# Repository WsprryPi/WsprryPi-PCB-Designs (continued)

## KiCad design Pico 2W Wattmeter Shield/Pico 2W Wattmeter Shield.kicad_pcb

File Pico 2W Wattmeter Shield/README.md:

# Pico 2W QRP Wattmeter Shield

A Raspberry Pi Pico 2 W shield with an ADL5904 RF power detector, ADS1115 ADC, and TPS7A2033 analog regulator. Open [Pico 2W Wattmeter Shield.kicad_pro](Pico%202W%20Wattmeter%20Shield.kicad_pro) in KiCad 10. Project libraries use `${KIPRJMOD}` paths.

The design is supplied **as is, without warranty**, under the repository's [MIT license](../LICENSE.md). It is an experimental system. Production use requires an operator who understands its limitations and requirements and verifies the assembled system's suitability. See the [repository notice](../README.md#experimental-use-and-warranty).

## Current design

The PCB is a two-layer, nominally 1.6 mm FR4 board with circuit components on F.Cu and U10's two female socket strips on B.Cu, matching the [Pico shield template](../Pico%202W%20Shield%20Template/README.md). It contains **37 footprints: 34 automatic SMT components, J30, U10, and one front silkscreen logo**. The components, including the R63/C61 pull-up supply filter, are placed and routed.

Assembled input match, accuracy, noise rejection, mechanical fit, and the soldering process are unqualified. ERC ignores single-use global labels, four-way junctions, simulation model issues, and footprint-filter mismatches; DRC has no ignored checks.

## Measurement path

`J30 → C30–C34 → RF_DET_IN → C40–C44 → RFIN/U40 → VRMS_RAW → R50/C50 → VRMS_FILTERED/U60 AIN0`

| Section | Saved design |
| --- | --- |
| RF input | J30; terminating low-power meter, with external attenuation for amplifier outputs |
| Coupling | Two banks of five parallel 100 nF C0G capacitors, nominally 500 nF per bank |
| Shunt load | R30–R34: five parallel 412 Ω resistors, nominally 82.4 Ω, plus the detector input branch |
| Input matching | The shunt is within 0.12% of ADI's 82.5 Ω reference; assembled input impedance is unmeasured |
| Intended frequency range | 136 kHz–450 MHz, covering 2200 m through 70 cm; assembled-board coverage is unqualified |
| Nominal detector range | −30 to +15 dBm, approximately 1 µW–31.6 mW; connector range requires calibration |
| ADC filter | R50 = 470 Ω, C50 = 22 µF X5R; nominal cutoff 15.4 Hz |

There is no onboard attenuation pad or qualified high-power overload protection. The two capacitor banks, buses, launch, and detector impedance form a frequency-dependent RF network. See [input range and measurement conditions](INPUT-RANGE.md). The printed current range is calculated for a nominal 50 Ω load, rather than a direct current measurement.

## Power

**The analog section requires VBUS.** U20 takes VBUS from Pico pin 40 and generates `ANALOG_3V3` for U40, U60, and the I²C pullups. C20 and C21 are 2.2 µF, 25 V X7R capacitors at the regulator input and output. C46/C47 decouple the detector, and C60 decouples the ADC. The Pico's 3V3 output is not connected to the analog rail.

USB normally supplies VBUS. Powering the Pico solely through VSYS leaves the analog section unpowered. An external VBUS source must respect the Pico's USB power arrangement and avoid conflicting supplies. Measurements require a valid analog rail and settled detector/filter output.

VBUS follows the lower perimeter, and the analog rail reaches the detector from below and the ADC/control branch from the right. Neither supply trace crosses the RF capacitor-bank area. R63/C61 isolate the pull-up supply branch. A common regulator and ground serve the analog and I²C loads; noise immunity to Pico activity is unmeasured.

## ADC and filtering

U60 uses AIN0 as a single-ended detector-voltage input. ADDR is grounded, giving I²C address 0x48. SDA uses GP4; SCL uses GP5 through the fitted R62 0 Ω jumper. R60/R61 are 4.7 kΩ pullups supplied through R63 = 47 Ω, with C61 = 1 µF X7R providing local bypass at their common supply node. This filter is present in both schematic and PCB. U40 and U60 receive `ANALOG_3V3` directly with their own decoupling. Unused ADC channels and ALERT/RDY have no-connect flags.

R63/C61 has a nominal **3.4 kHz** corner and approximately **65 mV** supply drop with both pull-ups low, assuming ideal low output levels. It provides local storage and supply isolation for switching currents. Its effect on the assembled noise floor is unmeasured; nominal attenuation at 50/60 Hz is negligible.

R50/C50 passes DC and attenuates changing voltage. Its ideal one-pole attenuation is about **10.6 dB at 50 Hz and 12.1 dB at 60 Hz**, with a 10.34 ms time constant and about 47.6 ms settling to 1%. Capacitor tolerance, bias, temperature, detector output impedance, and ADC loading affect these figures. It is not a mains notch filter, and there is no established system-level mains-rejection specification. C49 remains a separate 10 nF capacitor directly on VRMS.

The hardware provides one measurement channel. ADC range, conversion rate, timed averaging, and calibration coefficients are application settings; this repository does not establish a verified wattmeter firmware configuration.

## Current assembly and fabrication

Factory assembly comprises **34 components on F.Cu**: **C20–C21, C30–C34, C40–C50, C60–C61; R30–R34, R40, R50, R60–R63; U20, U40, U60**. This is 20 capacitors, 11 resistors, and three ICs. J30, two female sockets, and the Pico module are fitted by hand. U10 represents the combined 40-pad socket interface; schematic J10/J11 are pinless purchasing descriptions. The front logo and manual parts are excluded from automatic SMT assembly.

The **Shield purchasing BOM** preset uses `LCSC Part #`. All 34 schematic and PCB SMT parts have matching manufacturer, MPN, and LCSC identifiers. R30–R34 specify Viking ARG02BTC4120 / C2683017 in local 0402 footprints. R63 specifies YAGEO RC0402FR-0747RL / C137973 in 0402; C61 specifies YAGEO CC0603KRX7R8BB105 / C106858 in 0603. Factory BOM and placement exports must contain the same 34 references and correct U20/U40/U60 pin-1 orientation. The schematic contains the complete part selections. The input-range silkscreen displays J30 through a reference variable and follows reannotation.

Seven selected through vias use **0.60 mm copper / 0.25 mm drill** with filling/capping enabled, F-side untented, and B-side tented: five in U40's exposed ground pad and one each centered on R40 pad 1 and C48 pad 1. The unique drill size identifies this selective process. The 17 ordinary vias comprise five 0.50/0.20 mm, ten 0.60/0.30 mm, and two 0.80/0.40 mm vias. All 24 are through vias; the custom rules disallow blind, buried, and microvias. The ordinary ground-via drills beside C45/C47 have **0.15 mm nominal clearance** from the adjacent component solder-pad openings.

The required fabrication process is selective nonconductive epoxy filling, planarization, and copper capping. Its availability for this exact two-layer order is not confirmed. Four separate 0.65 × 0.65 mm F.Paste windows cover 52.16% of U40's 1.8 × 1.8 mm ground land. Supplier process acceptance, stencil thickness, and reflow conditions are assembly requirements.

- [Fabrication and assembly requirements](manufacturing-notes/ORDER-NOTES.txt)
- [Front assembly map](manufacturing-notes/ASSEMBLY-FRONT.svg)
- [Selective via-treatment drawing](manufacturing-notes/U1-VIA-TREATMENT.svg)
- [U40 exposed-pad and stencil geometry](U1-PASTE-WINDOWS.md)
- [SMA connector and board-edge fit](J1-CONNECTOR-NOTES.md)
- [Pico sockets and antenna notch](PICO-HEADERS-AND-NOTCH.md)

The manufacturing drawings identify their source PCB by SHA-256. Socket lead fit and mating height are unspecified. The PCB stackup's copper-finish field is `None`, and there are no dedicated board fiducials; finish and panel tooling belong in the order specification.

## Pico interface placement

U10 is locked at **(146.810, 90.750) mm, −90°, B.Cu**, and its `Raspberry Pi Pico 2W` group is locked. Its 40 pad positions match the template. The notch spans x = 164.46–173.46 mm and y = 82.86–96.86 mm, with a copper/component keepout on both layers.

In **Update PCB from Schematic**, leave **Re-link footprints to schematic symbols based on their reference designators** and **Override locks** unchecked. Normal symbol-ID matching preserves the interface identity and placement. [KiCad's update documentation](https://docs.kicad.org/10.0/en/pcbnew/pcbnew.html#updating_the_board_from_the_schematic) describes these options.

The two socket models belong to U10's combined footprint and use project-local paths. The reusable footprint contains the same references. The socket geometry is a generic preview, without a selected manufacturer or qualified mating stack.

## Libraries and 3D view

Local assets are in `pico-wattmeter.pretty/`, `pico-wattmeter.kicad_sym`, `pico-wattmeter.kicad_blocks/`, and `pico-wattmeter.3dshapes/`. See [footprint sources and licenses](pico-wattmeter.pretty/LIBRARY-SOURCES.md) and [model sources and limits](pico-wattmeter.3dshapes/README.md).

Select **View > 3D Viewer** in the PCB Editor. U40 uses the local CP-16-22 STEP model. U10 uses two local socket models. J30 uses the local illustrative Adafruit 1865 SMA model, pointing outward from the left board edge. Passives, U20, and U60 use installed KiCad models. All placed model references resolve in the checked KiCad installation.

The optional, unplaced Pico SMD footprint uses `${KIPRJMOD}/pico-2w-libs/Raspberrypi pico2 W.step`. That separate reference collection has [pin/pad, model-alignment, and provenance limitations](pico-2w-libs/README.md). It is not the placed socket interface.

`fabrication-toolkit-options.json` stores export preferences. KiCad sources contain the part identifiers, connectivity, layout, and assembly exclusions. Local preferences, backups, plugin state, and generated export directories are ignored by Git.

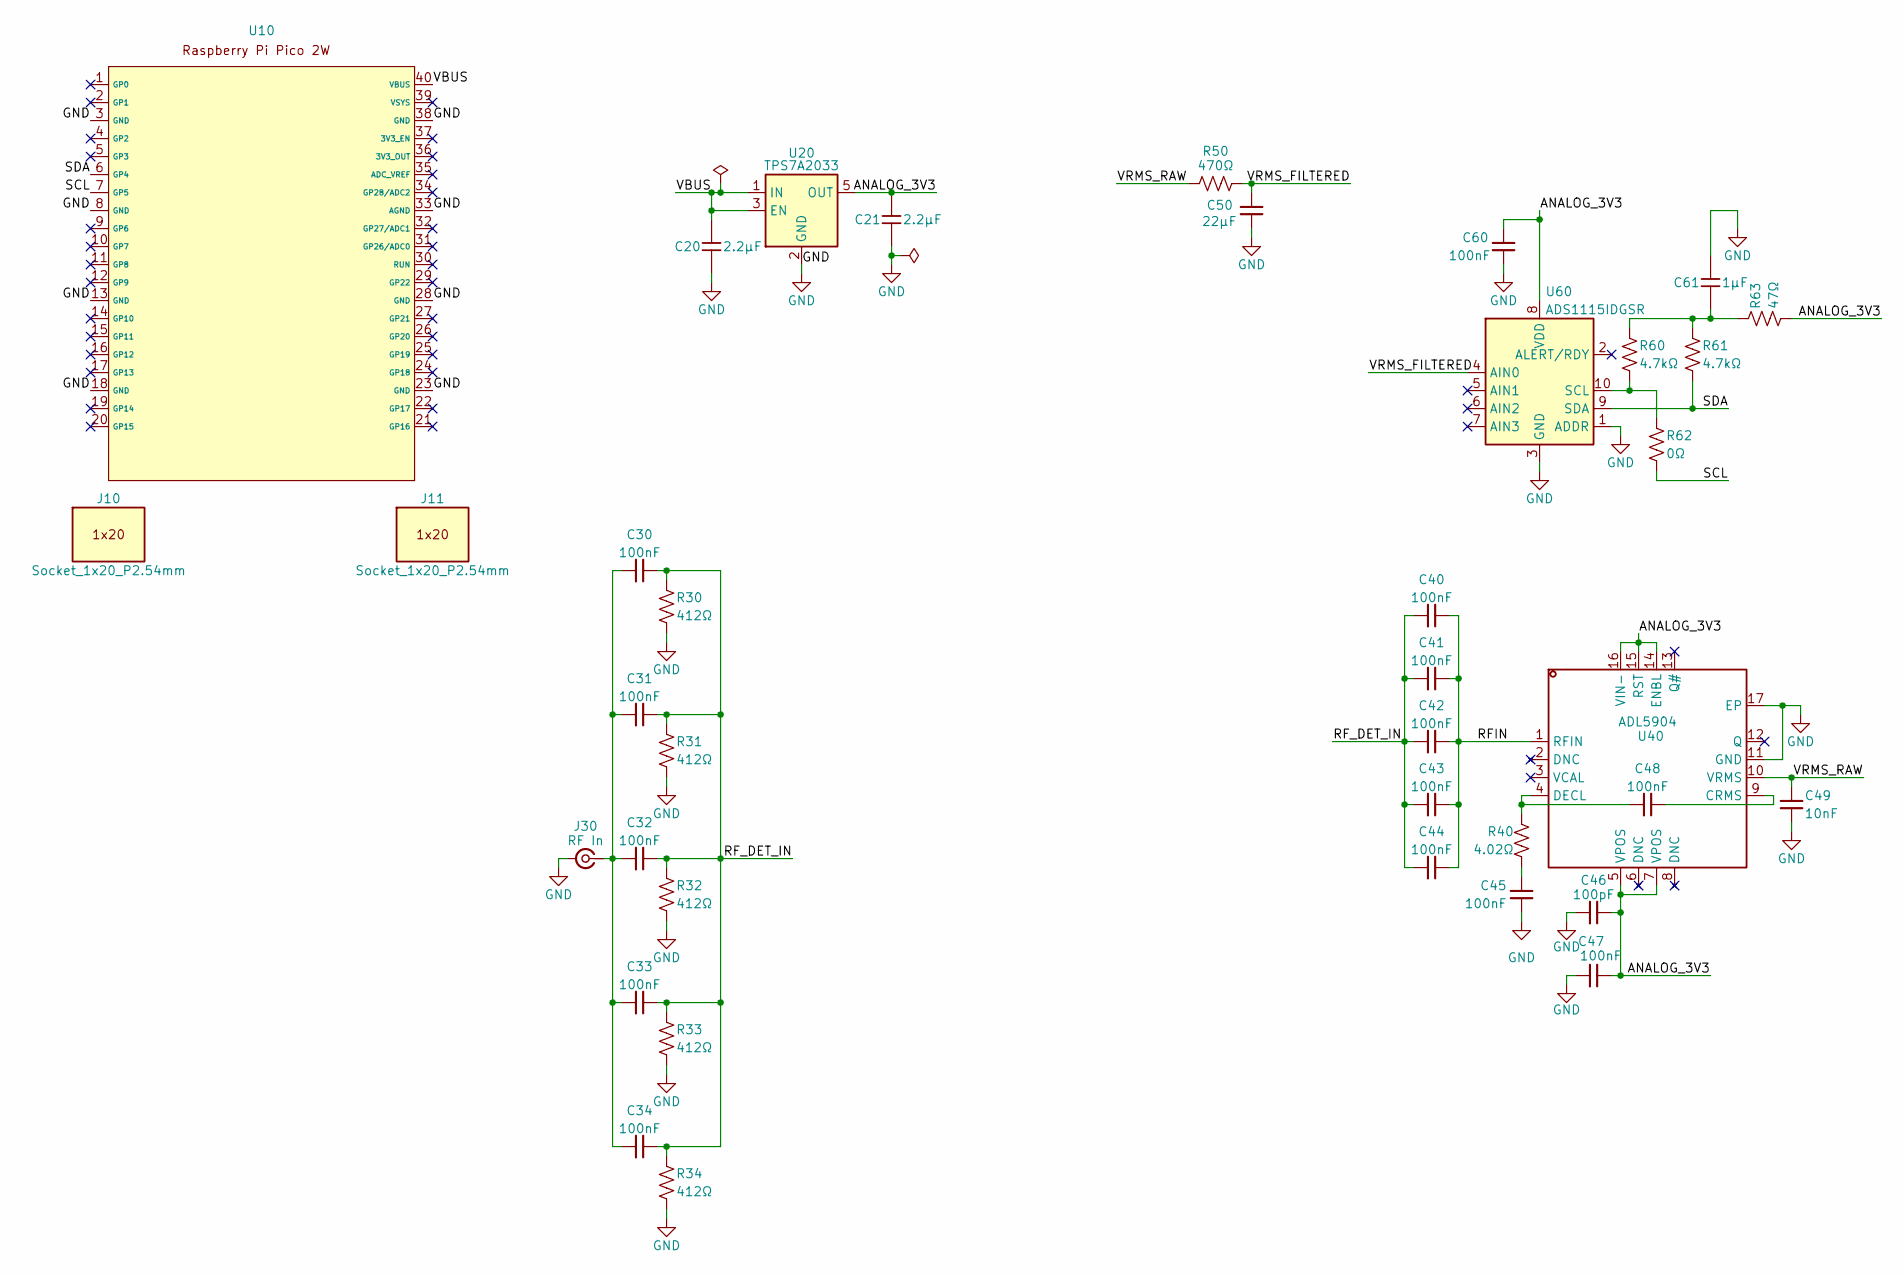
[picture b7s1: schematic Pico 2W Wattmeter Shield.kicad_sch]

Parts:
C20, C21: 2.2μF; C_0805_2012Metric; Tolerance 10%; Rating 25 V; MPN CC0805KKX7R8BB225; LCSC Part # C277470
C30, C31, C32, C33, C34, C40, C41, C42, C43, C44, C48: 100nF; C_1206_3216Metric; MPN 1206N104J500CT; LCSC Part # C170182
C45, C47, C60: 100nF; C_0402_1005Metric; MPN CL05B104KO5NNNC; LCSC Part # C1525
C46: 100pF; C_0402_1005Metric; MPN 0402CG101J500NT; LCSC Part # C1546
C49: 10nF; C_0402_1005Metric; MPN CL05B103KB5NNNC; LCSC Part # C15195
C50: 22µF; C_0805_2012Metric; MPN CL21A226MAYNNNE; LCSC Part # C602037
C61: 1μF; C_0603_1608Metric; Tolerance 10%; Rating 25 V; MPN CC0603KRX7R8BB105; LCSC Part # C106858
J10, J11: Socket_1x20_P2.54mm
J30: RF In; SMA_Adafruit_1865_EdgeMount; MPN 1865
R30, R31, R32, R33, R34: 412Ω; R_0402_1005Metric; MPN ARG02BTC4120; LCSC Part # C2683017
R40: 4.02Ω; R_0402_1005Metric; MPN FRC0402F4R02TS; LCSC Part # C55174786
R50: 470Ω; R_0402_1005Metric; MPN FRC0402F4700TS; LCSC Part # C2909361
R60, R61: 4.7kΩ; R_0402_1005Metric; MPN 0402WGF4701TCE; LCSC Part # C25900
R62: 0Ω; R_0805_2012Metric; MPN 0805W8F0000T5E; LCSC Part # C17477
R63: 47Ω; R_0402_1005Metric; MPN RC0402FR-0747RL; LCSC Part # C137973
U10: Raspberry_Pi_Pico_2W_Header
U20: TPS7A2033; SOT-23-5; Tolerance Datasheet; Rating 300 mA device rating; MPN TPS7A2033PDBVR; LCSC Part # C2862740
U40: ADL5904; QFN-16_L3.0-W3.0-P0.50-TL-EP1.8; MPN ADL5904ACPZN-R7; LCSC Part # C206813
U60: ADS1115IDGSR; TSSOP-10_3x3mm_P0.5mm; MPN ADS1115IDGSR; LCSC Part # C37593

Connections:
/ANALOG_3V3: C21.1, C46.2, C47.1, C60.2, R63.2, U20.5 (OUT), U40.5 (VPOS), U40.7 (VPOS), U40.14 (ENBL), U40.15 (RST), U40.16 (VIN-), U60.8 (VDD)
/RFIN: C40.2, C41.2, C42.2, C43.2, C44.2, U40.1 (RFIN)
/RF_DET_IN: C30.2, C31.2, C32.2, C33.2, C34.2, C40.1, C41.1, C42.1, C43.1, C44.1, R30.1, R31.1, R32.1, R33.1, R34.1
/SCL: R62.2, U10.7 (GP5)
/SDA: R61.2, U10.6 (GP4), U60.9 (SDA)
/VBUS: C20.1, U10.40 (VBUS), U20.1 (IN), U20.3 (EN)
/VRMS_FILTERED: C50.2, R50.2, U60.4 (AIN0)
/VRMS_RAW: C49.1, R50.1, U40.10 (VRMS)
GND: C20.2, C21.2, C45.2, C46.1, C47.2, C49.2, C50.1, C60.1, C61.1, J30.2 (GND), R30.2, R31.2, R32.2, R33.2, R34.2, U10.3 (GND), U10.8 (GND), U10.13 (GND), U10.18 (GND), U10.23 (GND), U10.28 (GND), U10.33 (AGND), U10.38 (GND), U20.2 (GND), U40.11 (GND), U40.17 (EP), U60.1 (ADDR), U60.3 (GND)
unnamed: C45.1, R40.2
unnamed: C61.2, R60.1, R61.1, R63.1
unnamed: C30.1, C31.1, C32.1, C33.1, C34.1, J30.1 (In)
unnamed: C48.2, U40.9 (CRMS)
unnamed: C48.1, R40.1, U40.4 (DECL)
unnamed: R60.2, R62.1, U60.10 (SCL)

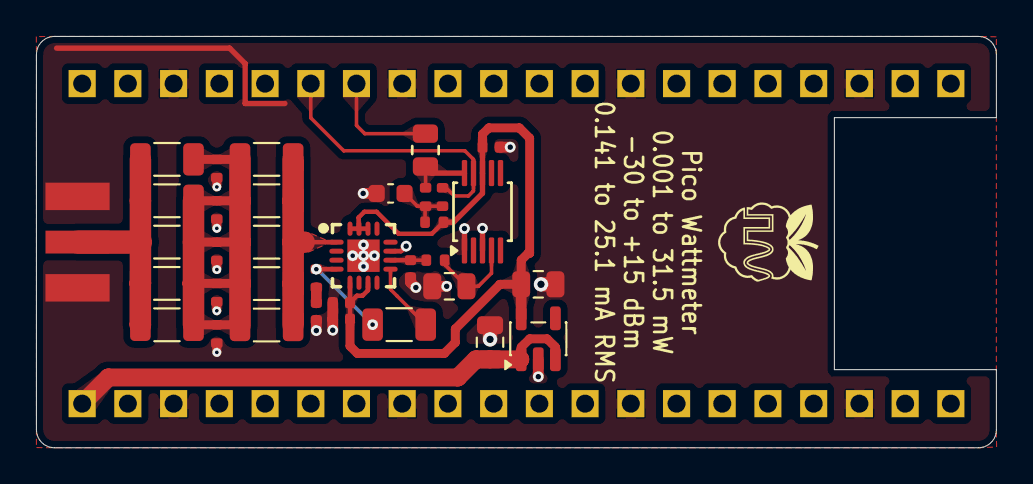
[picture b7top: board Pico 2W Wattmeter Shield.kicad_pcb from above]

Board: 2 copper layers, 53.3 x 22.9 mm, 37 parts (1 on the bottom side), 15 nets.

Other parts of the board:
LOGO2: Wsprry_Pi_Synth_Logo

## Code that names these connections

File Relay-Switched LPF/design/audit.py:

#!/usr/bin/env python3
"""Audit exported net membership, saved PCB parity, and default RF paths.

Uses only Python's standard library. Expected connections are enumerated here,
independently of the generator's connections.json. This is a topology audit,
not an electromagnetic, switching-transient, or physical test.
"""
from pathlib import Path
from collections import defaultdict, deque
import json
import re
import xml.etree.ElementTree as ET

root=Path(__file__).resolve().parents[1]
expected={}
def add(ref,net,*pins):
    for pin in pins: expected[(ref,str(pin))]=net
for pin,net in enumerate(['+5V','BAND5_N','BAND3_N','BAND4_N','BAND1_N','BAND2_N','GND','RFI','GND','RFO'],1): add('J1',net,pin)
add('W1','+5V',1);add('W1','RELAY_VPLUS',2)
add('W7','RFO',1);add('W7','FINAL_NC',2);add('W7','GND',3)
add('W8','GND',1);add('W8','GND_OUT',2)
add('W9','LPF1_OUT',1);add('W9','FINAL_RELAY_COM',2)
for ref in ['X1','X2','J26']: add(ref,'LPF1_OUT',1);add(ref,'GND_OUT',2)
for i in range(1,6):
    r=f'RL{i}'
    for pin,net in [(1,'RELAY_VPLUS'),(12,f'BAND{i}_N'),(8,'RFI'),(9,f'LPF{i}_IN'),(10,'FINAL_NC' if i==1 else 'GND'),(3,'GND'),(4,'FINAL_RELAY_COM' if i==1 else f'LPF{i}_OUT'),(5,f'RELAY{i}_OUT')]: add(r,net,pin)
    add(f'D{i}','RELAY_VPLUS',1);add(f'D{i}',f'BAND{i}_N',2)
    add(f'J{i*2}','GND',1,2);add(f'J{i*2}',f'LPF{i}_IN',3,4)
    add(f'J{i*2+1}',f'LPF{i}_OUT',1,2);add(f'J{i*2+1}','GND_OUT' if i==1 else 'GND',3,4)
    add(f'W{i+1}',f'RELAY{i}_OUT',1);add(f'W{i+1}','RFO',2);add(f'W{i+1}',f'ANT{i}',3)
    add(f'J{20+i}',f'ANT{i}',1);add(f'J{20+i}','GND',2)

doc=ET.parse(root/'generated/connectivity.xml')
actual={}
for net in doc.findall('.//nets/net'):
    for node in net.findall('node'): actual[(node.get('ref'),node.get('pin'))]=net.get('name').lstrip('/')
assert actual==expected, f'Schematic mismatch: {set(actual.items()) ^ set(expected.items())}'

def parse(text):
    stack=[]; result=None
    for token in re.findall(r'\(|\)|"(?:\\.|[^"\\])*"|[^\s()]+',text):
        if token=='(':
            item=[]
            if stack: stack[-1].append(item)
            stack.append(item)
        elif token==')': result=stack.pop()
        else: stack[-1].append(json.loads(token) if token.startswith('"') else token)
    return result
def children(obj,key): return [v for v in obj if isinstance(v,list) and v and v[0]==key]
pcb=parse((root/'Relay-Switched LPF.kicad_pcb').read_text())
board={}
for fp in children(pcb,'footprint'):
    ref=next(v[2] for v in children(fp,'property') if v[1]=='Reference')
    if ref.startswith('H'): continue
    for pad in children(fp,'pad'):
        net=children(pad,'net')[0][1].lstrip('/')
        key=(ref,pad[1])
        assert key not in board or board[key]==net, f'Duplicate numbered pad has conflicting net: {key}'
        board[key]=net
assert board==expected, f'Board mismatch: {set(board.items()) ^ set(expected.items())}'

paths={}
for selected in range(6):
    graph=defaultdict(list)
    def edge(a,bb,label=''):
        graph[a].append((bb,label));graph[bb].append((a,label))
    for i in range(1,6):
        r=f'RL{i}'
        for com,no,nc in [(9,8,10),(4,5,3)]:
            edge(expected[(r,str(com))],expected[(r,str(no if i==selected else nc))])
        edge(f'LPF{i}_IN',f'LPF{i}_OUT',f'LPF{i}')
    for ref in ['W1','W3','W4','W5','W6','W7']: edge(expected[(ref,'1')],expected[(ref,'2')])
    start='RFO' if selected==0 else 'RFI'
    queue=deque([(start,[])]); seen={start}; found=None
    while queue:
        node,filters=queue.popleft()
        if node=='LPF1_OUT': found=filters;break
        for target,label in graph[node]:
            if target not in seen:
                seen.add(target);queue.append((target,filters+([label] if label else [])))
    wanted=['LPF1'] if selected in [0,1] else [f'LPF{selected}','LPF1']
    assert found==wanted,(selected,found,wanted)
    # Check grounding separately without stopping the traversal at the output.
    queue=deque([start]);seen={start}
    while queue:
        for target,_ in graph[queue.popleft()]:
            if target not in seen: seen.add(target);queue.append(target)
    assert 'GND' not in seen and 'GND_OUT' not in seen, f'Selected RF path grounded in state {selected}'
    paths[selected]=found
print(f'PASS: {len(expected)} unique component pins, {len(set(expected.values()))} nets; schematic and PCB agree.')
print('PASS: default filter paths for external band 0 and selected bands 1-5:',paths)

# The delivered folder must resolve every part without global CAD libraries.
local='relay-switched-lpf'
symbols=parse((root/(local+'.kicad_sym')).read_text())
symbol_names={v[1] for v in children(symbols,'symbol')}
schematic=parse((root/'Relay-Switched LPF.kicad_sch').read_text())
for inst in children(schematic,'symbol'):
    lib_id=children(inst,'lib_id')[0][1]
    assert lib_id.startswith(local+':') and lib_id.split(':',1)[1] in symbol_names,lib_id
bare={*[f'H{i}' for i in range(1,5)],*[f'J{i}' for i in range(21,27)],'W2','W8','W9'}
model_count=0;footprint_count=0;assets=set()
for fp in children(pcb,'footprint'):
    footprint_count+=1
    ref=next(v[2] for v in children(fp,'property') if v[1]=='Reference')
    assert fp[1].startswith(local+':'),(ref,fp[1])
    name=fp[1].split(':',1)[1]
    assert (root/(local+'.pretty')/(name+'.kicad_mod')).exists(),(ref,name)
    models=children(fp,'model')
    assert bool(models)==(ref not in bare),(ref,'unexpected model population')
    for model in models:
        assert model[1].startswith('${KIPRJMOD}/'),model[1]
        target=root/model[1][len('${KIPRJMOD}/'):]
        assert target.is_file(),target
        model_count+=1;assets.add(target.name)
for footprint in (root/(local+'.pretty')).glob('*.kicad_mod'):
    for model in children(parse(footprint.read_text()),'model'):
        assert model[1].startswith('${KIPRJMOD}/'),(footprint,model[1])
        assert (root/model[1][len('${KIPRJMOD}/'):]).is_file(),(footprint,model[1])
print(f'PASS: {footprint_count} local footprints; {model_count} model instances / {len(assets)} local assets; all schematic symbols local.')

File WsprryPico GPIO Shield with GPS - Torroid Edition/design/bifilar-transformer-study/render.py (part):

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
# A single series-aiding winding stack makes the supply / tap / RF end explicit.
C.saveState(); C.transform(1,0,0,0.90,0,61.4)
label('AMP_5V_SW',40,626,9,True)
line(40,614,160,614);C.rect(160,607,60,14,stroke=1,fill=0);line(220,614,330,614)
label('R64 1 ohm',158,632,9,True);label('1%, >=0.25 W',153,594,8)
dot(120,614);label('TP61 (+)',99,647,8)
dot(285,614);label('TP62 (-)',264,647,8)
line(330,614,330,594);label('AMP_XFMR_FEED',340,628,9,True)
line(330,614,455,614);line(455,614,455,591);vcap(455,576);ground(455,559)
line(455,614,525,614);line(525,614,525,591);vcap(525,576);ground(525,559)
label('C62',441,540,8,True);label('100 nF',436,528,8)
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label('A: 15 turns',354,555,9,True)
label('2: A finish',342,516,9)
dot(330,510);line(330,510,180,510);line(180,510,180,477)
label('AMP_DRAIN',191,488,9,True)
coil(330,510);dot(317,496,3);label('3: B start',342,490,9)
label('B: 15 turns',354,463,9,True)
label('4: B finish',342,431,9)
line(330,426,330,405);line(330,405,428,405)
line(428,394,428,416);line(435,394,435,416);line(435,405,550,405)
label('AMP_RF_XFMR',340,390,8)
label('C64, C66-C69',385,374,9,True);label('5 x 100 nF C0G, 50 V',378,360,8)
label('J61 SMA',500,425,9,True);label('to band LPF',491,390,8);label('and 50 ohms',490,378,8)
C.rect(143,432,74,45,stroke=1,fill=0);label('Q61',163,459,10,True);label('BS170',160,444,9)
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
